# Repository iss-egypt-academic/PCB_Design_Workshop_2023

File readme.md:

# ISS Egypt PCB Desgin Workshop 

## Voltage Regulator

### Schematic

### 3D View

## Arduino Nano Shield 

### Schematic

### 3D View

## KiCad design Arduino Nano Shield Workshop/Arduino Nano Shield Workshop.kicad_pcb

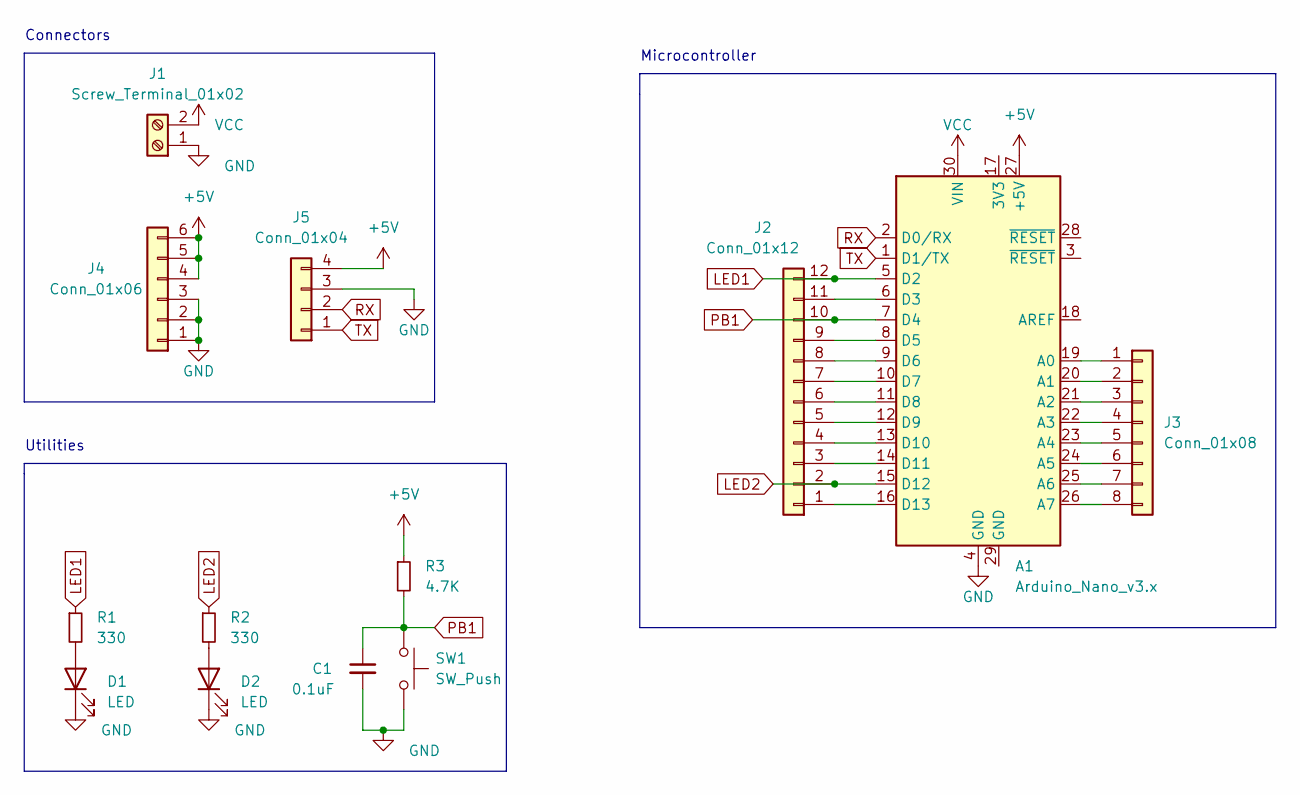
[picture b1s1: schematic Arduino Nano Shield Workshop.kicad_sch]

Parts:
A1: Arduino_Nano_v3.x; Arduino_Nano
C1: 0.1uF; C_Elec_4x5.4
D1, D2: LED; LED_0603_1608Metric
J1: Screw_Terminal_01x02; TerminalBlock_bornier-2_P5.08mm
J2: Conn_01x12; PinHeader_1x12_P1.00mm_Vertical
J3: Conn_01x08; PinHeader_1x08_P1.00mm_Vertical
J4: Conn_01x06; PinHeader_1x06_P1.00mm_Vertical
J5: Conn_01x04; PinHeader_1x04_P1.00mm_Vertical
R1, R2: 330; R_0805_2012Metric
R3: 4.7K; R_0805_2012Metric
SW1: SW_Push; SW_PUSH_6mm

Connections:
+5V: A1.27 (+5V), J4.4, J4.5, J4.6, J5.4, R3.1
GND: A1.4 (GND), C1.2, D1.1 (K), D2.1 (K), J1.1, J4.1, J4.2, J4.3, J5.3, SW1.2
LED1: A1.5 (D2), J2.12, R1.1
LED2: A1.15 (D12), J2.2, R2.1
unnamed: A1.19 (A0), J3.1
unnamed: A1.20 (A1), J3.2
unnamed: A1.21 (A2), J3.3
unnamed: A1.22 (A3), J3.4
unnamed: A1.23 (A4), J3.5
unnamed: A1.24 (A5), J3.6
unnamed: A1.25 (A6), J3.7
unnamed: A1.26 (A7), J3.8
unnamed: A1.6 (D3), J2.11
unnamed: A1.8 (D5), J2.9
unnamed: A1.9 (D6), J2.8
unnamed: A1.10 (D7), J2.7
unnamed: A1.11 (D8), J2.6
unnamed: A1.12 (D9), J2.5
unnamed: A1.13 (D10), J2.4
unnamed: A1.14 (D11), J2.3
unnamed: A1.16 (D13), J2.1
unnamed: D1.2 (A), R1.2
unnamed: D2.2 (A), R2.2
PB1: A1.7 (D4), C1.1, J2.10, R3.2, SW1.1
RX: A1.2 (D0/RX), J5.2
TX: A1.1 (D1/TX), J5.1
VCC: A1.30 (VIN), J1.2

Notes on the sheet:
Utilities
Microcontroller
Connectors

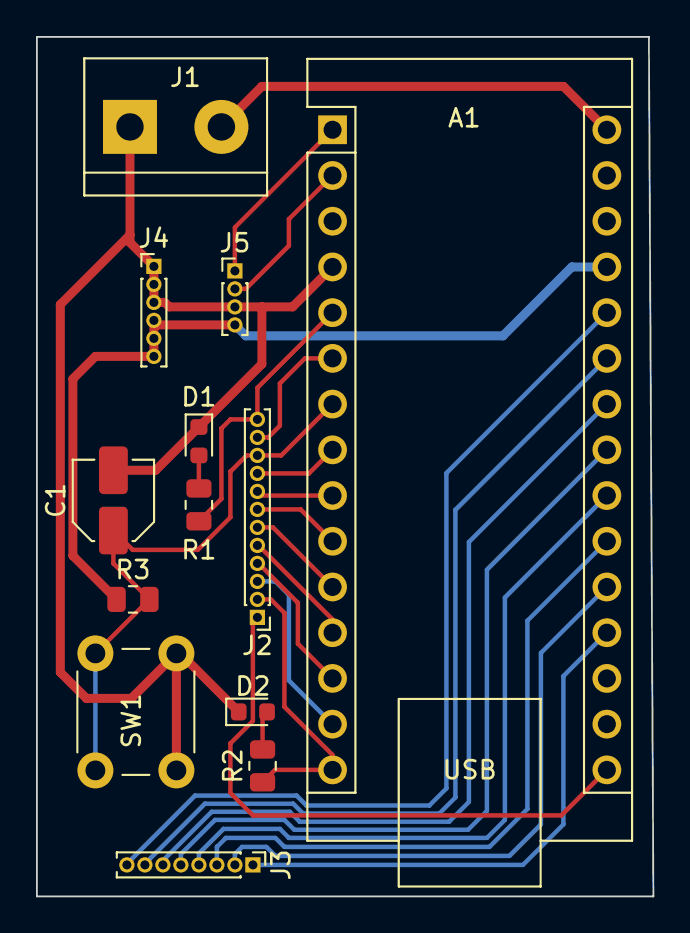
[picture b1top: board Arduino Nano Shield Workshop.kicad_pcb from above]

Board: 2 copper layers, 34.2 x 47.8 mm, 13 parts (0 on the bottom side), 27 nets.

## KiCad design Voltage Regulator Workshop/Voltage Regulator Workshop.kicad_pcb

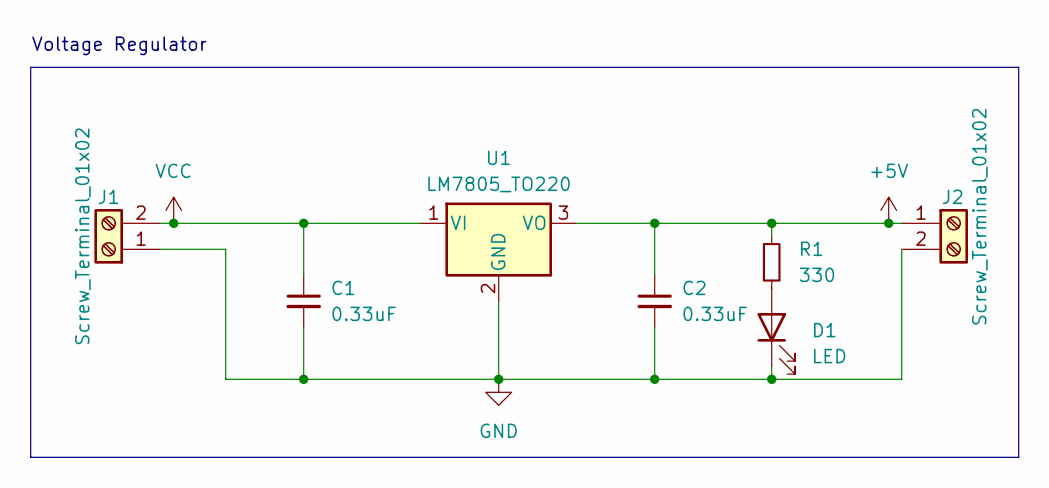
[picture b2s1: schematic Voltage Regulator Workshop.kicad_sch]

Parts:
C1, C2: 0.33uF; C_Elec_4x5.4
D1: LED; LED_0603_1608Metric
J1, J2: Screw_Terminal_01x02; TerminalBlock_bornier-2_P5.08mm
R1: 330; R_0805_2012Metric
U1: LM7805_TO220; TO-220-3_Vertical

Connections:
+5V: C2.1, J2.1, R1.1, U1.3 (VO)
GND: C1.2, C2.2, D1.1 (K), J1.1, J2.2, U1.2 (GND)
unnamed: D1.2 (A), R1.2
VCC: C1.1, J1.2, U1.1 (VI)

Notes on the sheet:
Voltage Regulator

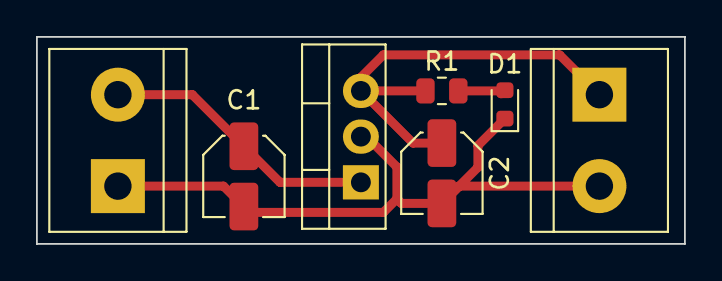
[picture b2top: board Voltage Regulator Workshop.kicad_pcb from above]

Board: 2 copper layers, 36.0 x 11.5 mm, 7 parts (0 on the bottom side), 4 nets.

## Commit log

2024-11-20 created repo
2024-11-21 added readme
